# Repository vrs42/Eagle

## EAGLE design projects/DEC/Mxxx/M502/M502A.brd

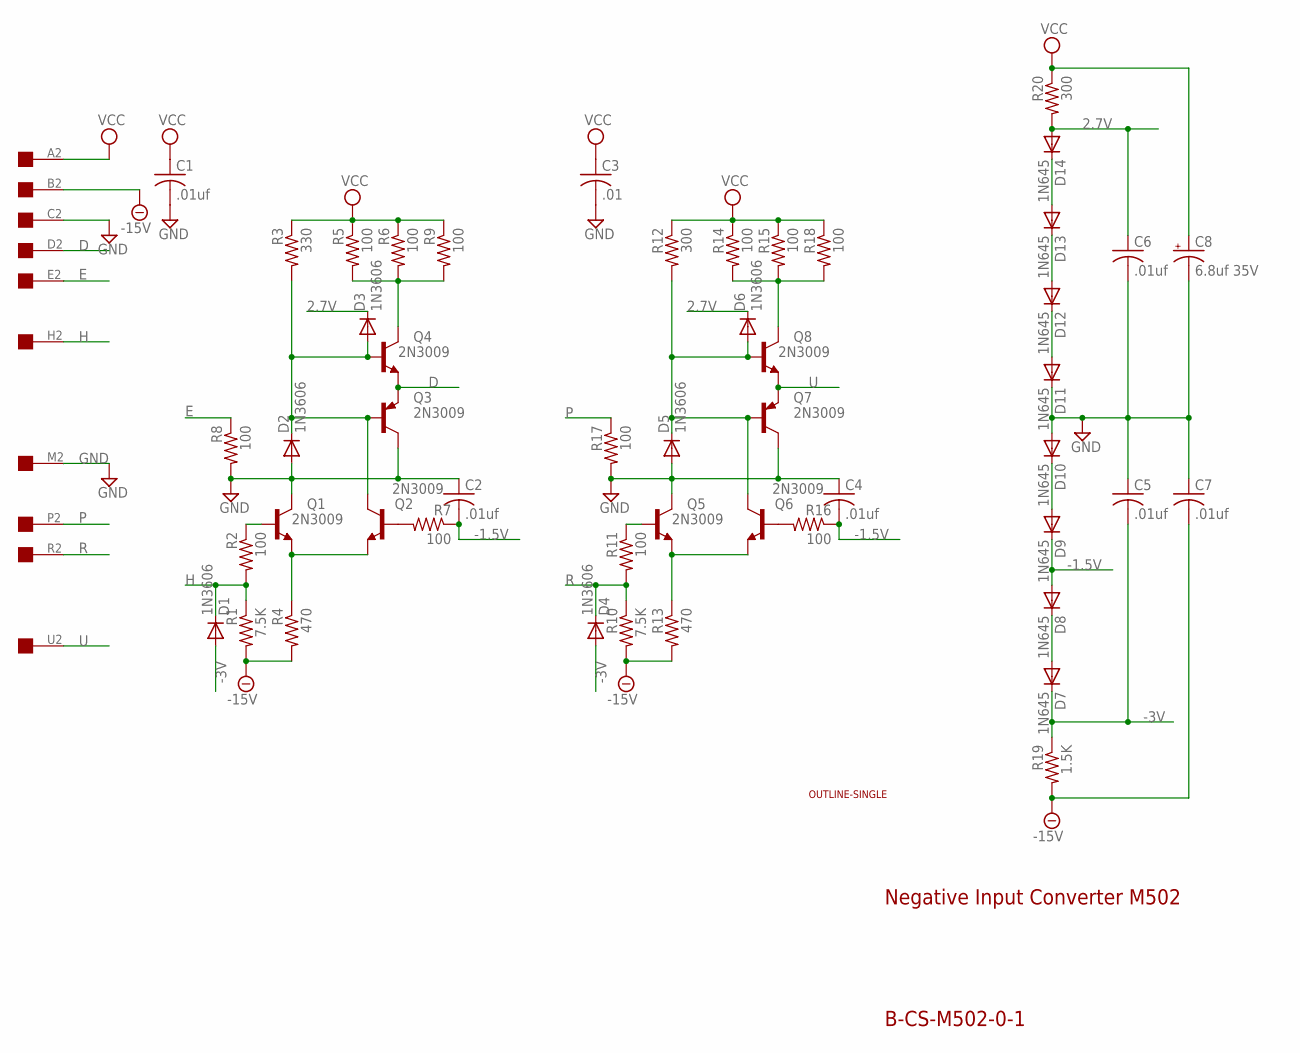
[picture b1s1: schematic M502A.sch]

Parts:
C1, C2, C4, C5, C6, C7: .01uf; C050-025X075
C3: .01; C050-025X075
C8: 6.8uf 35V; E15-5
D1, D2, D3, D4, D5, D6: 1N3606; DO41-10
D7, D8, D9, D10, D11, D12, D13, D14: 1N645; DO41-10
Q1, Q2, Q3, Q4, Q5, Q6, Q7, Q8: 2N3009; TO39
R1, R10: 7.5K; 0207/10
R2, R5, R6, R7, R8, R9, R11, R14, R15, R16, R17, R18: 100; 0207/10
R3: 330; 0207/10
R4, R13: 470; 0207/10
R12, R20: 300; 0207/10
R19: 1.5K; 0207/10
U$1: EDGE-1; EDGE-CON1
U$2: OUTLINE-SINGLE; SINGLE

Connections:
2.7V: C6.1, D3.C, D6.C, D14.A, R20.2
-1.5V: C2.2, C4.2, D8.A, D9.C, R7.1, R16.1
-3V: C5.2, D1.A, D4.A, D7.C, R19.1
-15V: C7.2, R1.2, R4.2, R10.2, R13.2, R19.2, U$1.B2
D: Q3.1 (E), Q4.1 (E), U$1.D2
E: R8.1, U$1.E2
GND: C1.2, C2.1, C3.2, C4.1, C5.1, C6.2, C7.1, C8.-, D2.A, D5.A, D10.A, D11.C, Q1.3 (C), Q3.3 (C), Q5.3 (C), Q7.3 (C), R8.2, R17.2, U$1.C2, U$1.M2
H: D1.C, R1.1, R2.2, U$1.H2
unnamed: Q4.3 (C), R5.2, R6.2, R9.2
unnamed: Q1.2 (B), R2.1
unnamed: Q5.1 (E), Q6.1 (E), R13.1
unnamed: Q1.1 (E), Q2.1 (E), R4.1
unnamed: D11.A, D12.C
unnamed: D2.C, D3.A, Q2.3 (C), Q3.2 (B), Q4.2 (B), R3.2
unnamed: D7.A, D8.C
unnamed: Q5.2 (B), R11.1
unnamed: D5.C, D6.A, Q6.3 (C), Q7.2 (B), Q8.2 (B), R12.2
unnamed: Q2.2 (B), R7.2
unnamed: D12.A, D13.C
unnamed: D9.A, D10.C
unnamed: Q8.3 (C), R14.2, R15.2, R18.2
unnamed: D13.A, D14.C
unnamed: Q6.2 (B), R16.2
P: R17.1, U$1.P2
R: D4.C, R10.1, R11.2, U$1.R2
U: Q7.1 (E), Q8.1 (E), U$1.U2
VCC: C1.1, C3.1, C8.+, R3.1, R5.1, R6.1, R9.1, R12.1, R14.1, R15.1, R18.1, R20.1, U$1.A2

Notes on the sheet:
Negative Input Converter M502
B-CS-M502-0-1

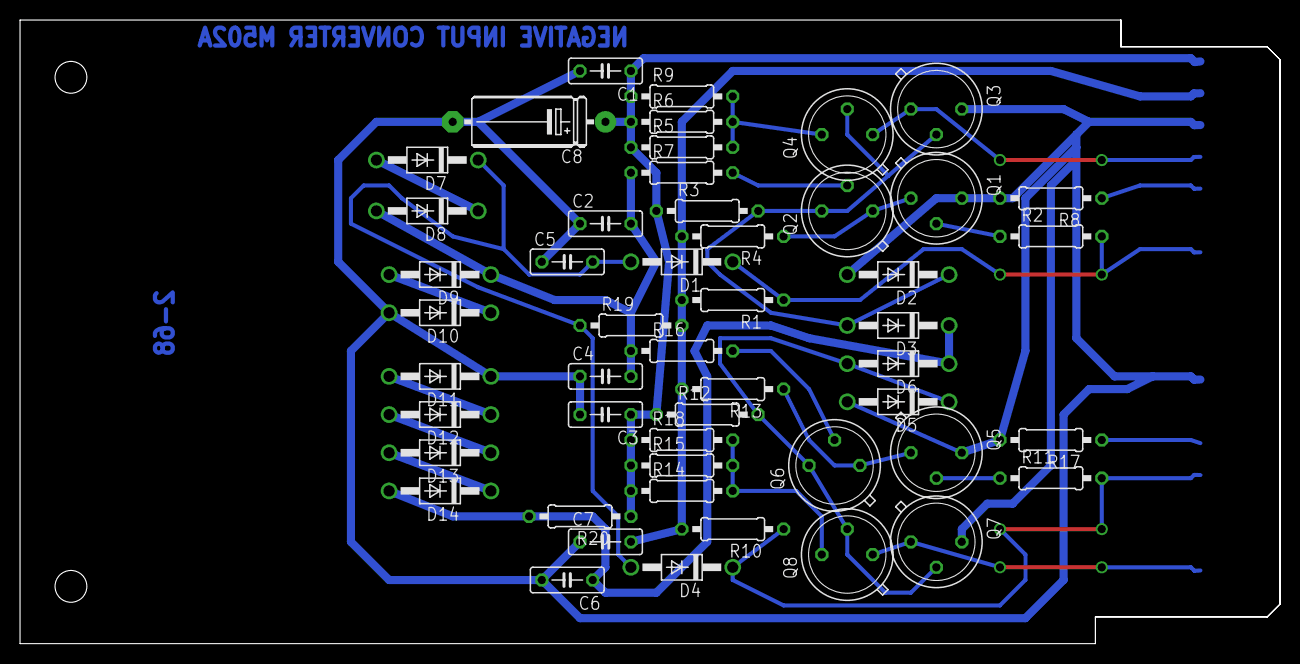
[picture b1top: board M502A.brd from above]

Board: 2 copper layers, 125.7 x 62.2 mm, 52 parts (0 on the bottom side), 27 nets.

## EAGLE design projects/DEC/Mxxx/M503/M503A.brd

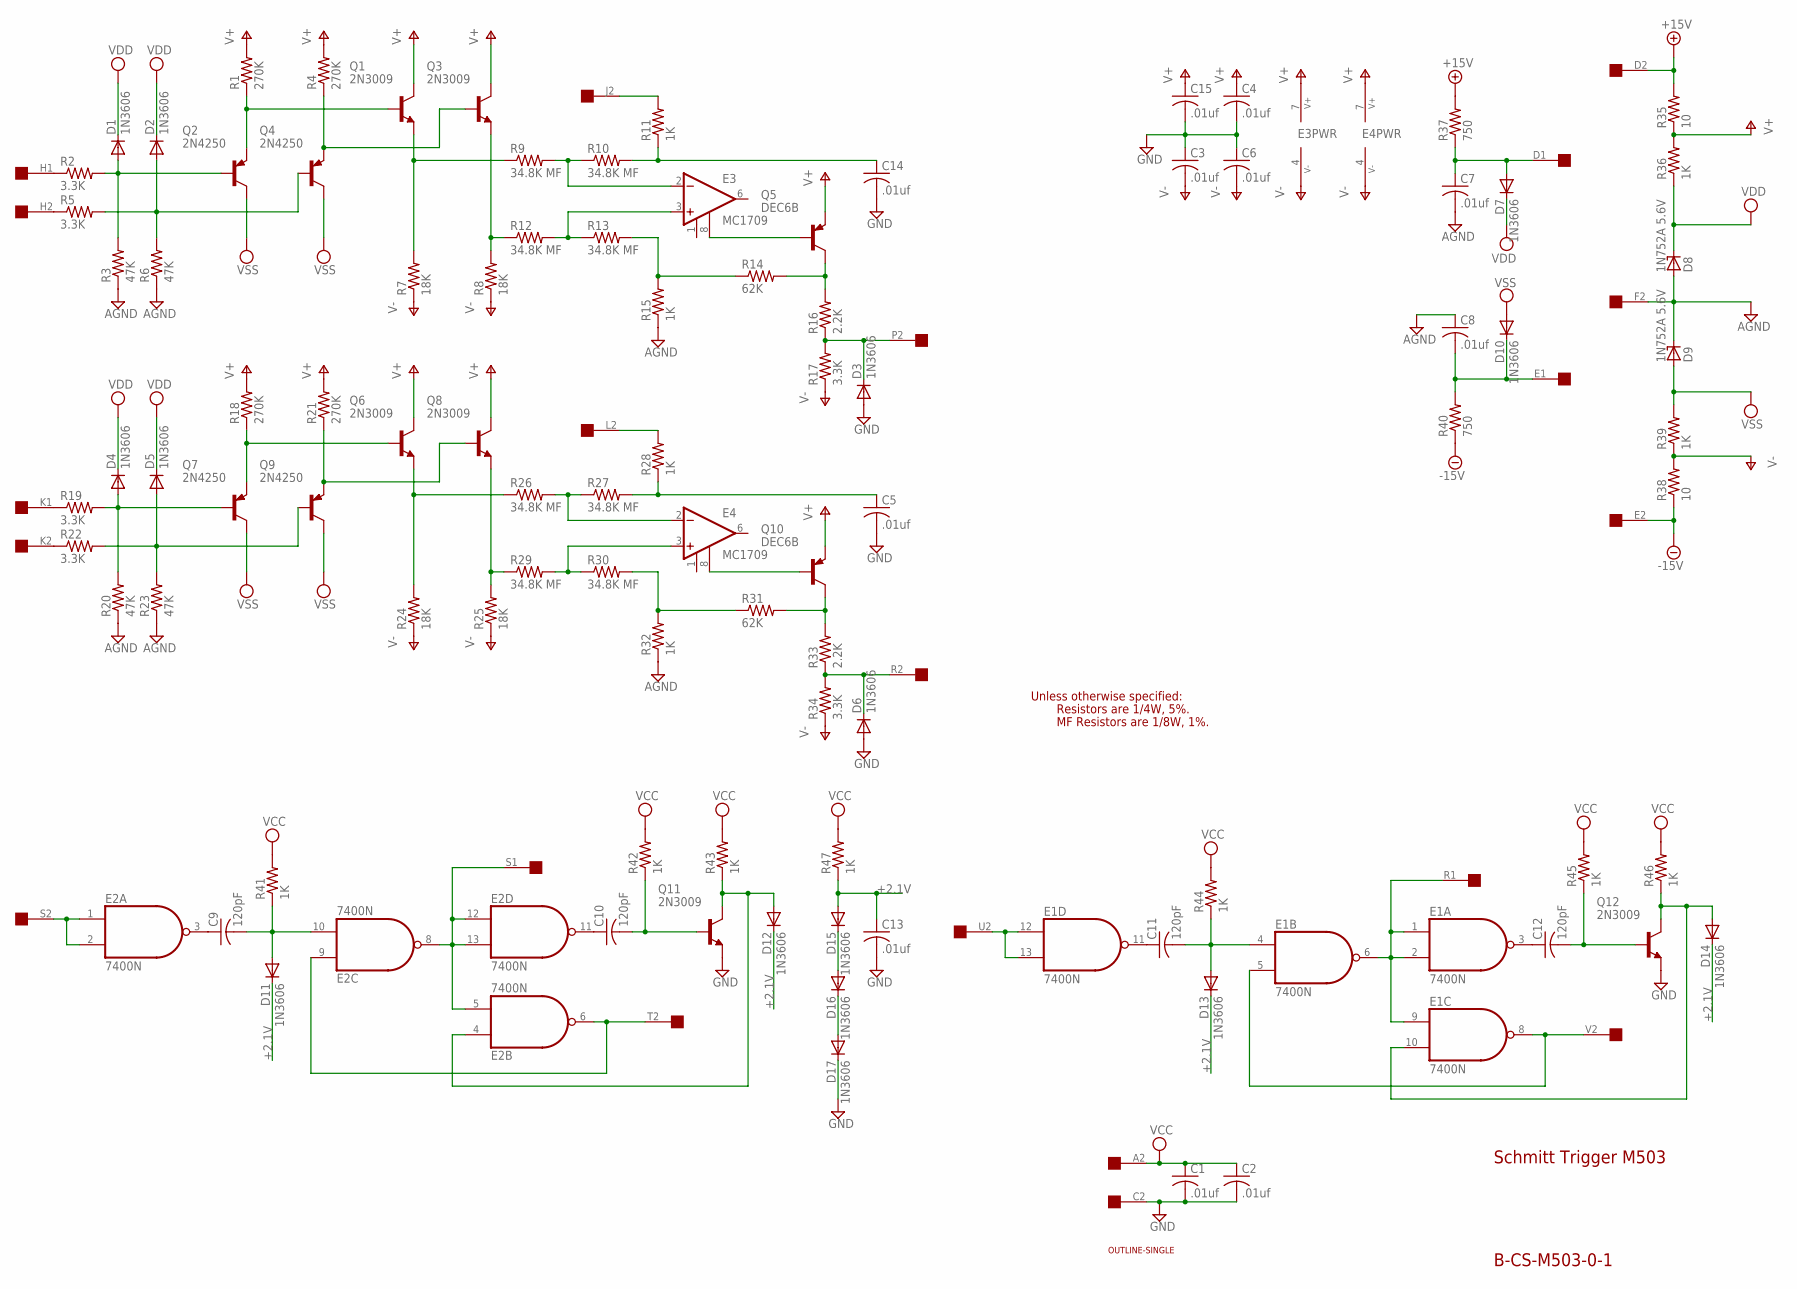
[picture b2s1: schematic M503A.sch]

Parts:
C1, C2: .01uf; C075-032X103
C3, C4, C5, C6, C7, C8, C13, C14, C15: .01uf; C050-025X075
C9, C10, C11, C12: 120pF; C050-025X075
D1, D2, D3, D4, D5, D6, D7, D10, D11, D12, D13, D14, D15, D16, D17: 1N3606; DO35-10
D8, D9: 1N752A 5.6V; DO35Z10
E1, E2: 7400N; DIL14
E3: MC1709; TO99C
E4: MC1709; TO99B
Q1, Q3, Q6, Q8, Q11, Q12: 2N3009; TO39
Q2, Q4, Q7, Q9: 2N4250; TO39
Q5, Q10: DEC6B; TO39
R1, R4, R18, R21: 270K; 0207/10
R2, R5, R17, R19, R22, R34: 3.3K; 0207/10
R3, R6, R20, R23: 47K; 0207/10
R7, R8, R24, R25: 18K; 0207/10
R9, R10, R12, R13, R26, R27, R29, R30: 34.8K MF; 0207/10
R11, R15, R28, R32, R36, R39, R41, R42, R43, R44, R45, R46, R47: 1K; 0207/10
R14, R31: 62K; 0207/10
R16, R33: 2.2K; 0207/10
R35, R38: 10; 0207/10
R37, R40: 750; 0207/10
U$2: SINGLE; EDGE-CON2
U$4: OUTLINE-SINGLE; SINGLE

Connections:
+2.1V: C13.1, D11.C, D12.C, D13.C, D14.C, D15.A, R47.1
+15V: R35.2, R37.2, U$2.D2
-15V: R38.1, R40.1, U$2.E2
AGND: C7.2, C8.1, D8.A, D9.C, R3.1, R6.1, R15.1, R20.1, R23.1, R32.1, U$2.F2
GND: C1.2, C2.2, C3.1, C4.2, C5.2, C6.1, C13.2, C14.2, C15.2, D3.A, D6.A, D17.C, E1.7 (GND), E2.7 (GND), Q11.1 (E), Q12.1 (E), U$2.C2
unnamed: E1.1 (I0), E1.2 (I1), E1.6 (O), E1.9 (I0), U$2.R1
unnamed: E1.5 (I1), E1.8 (O), U$2.V2
unnamed: E1.12 (I0), E1.13 (I1), U$2.U2
unnamed: C11.1, E1.11 (O)
unnamed: C11.2, D13.A, E1.4 (I0), R44.1
unnamed: D14.A, E1.10 (I1), Q12.3 (C), R46.1
unnamed: Q6.2 (B), Q7.1 (E), R18.1
unnamed: C12.2, Q12.2 (B), R45.1
unnamed: C12.1, E1.3 (O)
unnamed: E2.5 (I1), E2.8 (O), E2.12 (I0), E2.13 (I1), U$2.S1
unnamed: E2.6 (O), E2.9 (I0), U$2.T2
unnamed: C9.1, E2.3 (O)
unnamed: C9.2, D11.A, E2.10 (I1), R41.1
unnamed: E2.1 (I0), E2.2 (I1), U$2.S2
unnamed: Q1.2 (B), Q2.1 (E), R1.1
unnamed: C10.2, Q11.2 (B), R42.1
unnamed: C10.1, E2.11 (O)
unnamed: D12.A, E2.4 (I0), Q11.3 (C), R43.1
unnamed: D1.A, Q2.2 (B), R2.2, R3.2
unnamed: R2.1, U$2.H1
unnamed: Q1.1 (E), R7.2, R9.1
unnamed: R5.1, U$2.H2
unnamed: D2.A, Q4.2 (B), R5.2, R6.2
unnamed: Q3.2 (B), Q4.1 (E), R4.1
unnamed: Q3.1 (E), R8.2, R12.1
unnamed: E3.3 (+IN), R12.2, R13.1
unnamed: E3.2 (-IN), R9.2, R10.1
unnamed: C14.1, R10.2, R11.1
unnamed: R13.2, R14.1, R15.2
unnamed: E3.8 (CMP), Q5.2 (B)
unnamed: Q5.3 (C), R14.2, R16.2
unnamed: R11.2, U$2.J2
unnamed: D3.C, R16.1, R17.2, U$2.P2
unnamed: D4.A, Q7.2 (B), R19.2, R20.2
unnamed: R22.1, U$2.K2
unnamed: Q6.1 (E), R24.2, R26.1
unnamed: R19.1, U$2.K1
unnamed: D5.A, Q9.2 (B), R22.2, R23.2
unnamed: Q8.2 (B), Q9.1 (E), R21.1
unnamed: Q8.1 (E), R25.2, R29.1
unnamed: E4.3 (+IN), R29.2, R30.1
unnamed: E4.2 (-IN), R26.2, R27.1
unnamed: C5.1, R27.2, R28.1
unnamed: R30.2, R31.1, R32.2
unnamed: E4.8 (CMP), Q10.2 (B)
unnamed: Q10.3 (C), R31.2, R33.2
unnamed: R28.2, U$2.L2
unnamed: D6.C, R33.1, R34.2, U$2.R2
unnamed: C7.1, D7.A, R37.1, U$2.D1
unnamed: C8.2, D10.C, R40.2, U$2.E1
unnamed: D15.C, D16.A
unnamed: D16.C, D17.A
V+: C4.1, C15.1, E3.7 (+10V), E4.7 (+10V), Q1.3 (C), Q3.3 (C), Q5.1 (E), Q6.3 (C), Q8.3 (C), Q10.1 (E), R1.2, R4.2, R18.2, R21.2, R35.1, R36.2
V-: C3.2, C6.2, E3.4 (-15V), E4.4 (-15V), R7.1, R8.1, R17.1, R24.1, R25.1, R34.1, R38.2, R39.1
VCC: C1.1, C2.1, E1.14 (VCC), E2.14 (VCC), R41.2, R42.2, R43.2, R44.2, R45.2, R46.2, R47.2, U$2.A2
VDD: D1.C, D2.C, D4.C, D5.C, D7.C, D8.C, R36.1
VSS: D9.A, D10.A, Q2.3 (C), Q4.3 (C), Q7.3 (C), Q9.3 (C), R39.2

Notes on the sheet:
Schmitt Trigger M503
B-CS-M503-0-1
Unless otherwise specified:
Resistors are 1/4W, 5%.
MF Resistors are 1/8W, 1%.

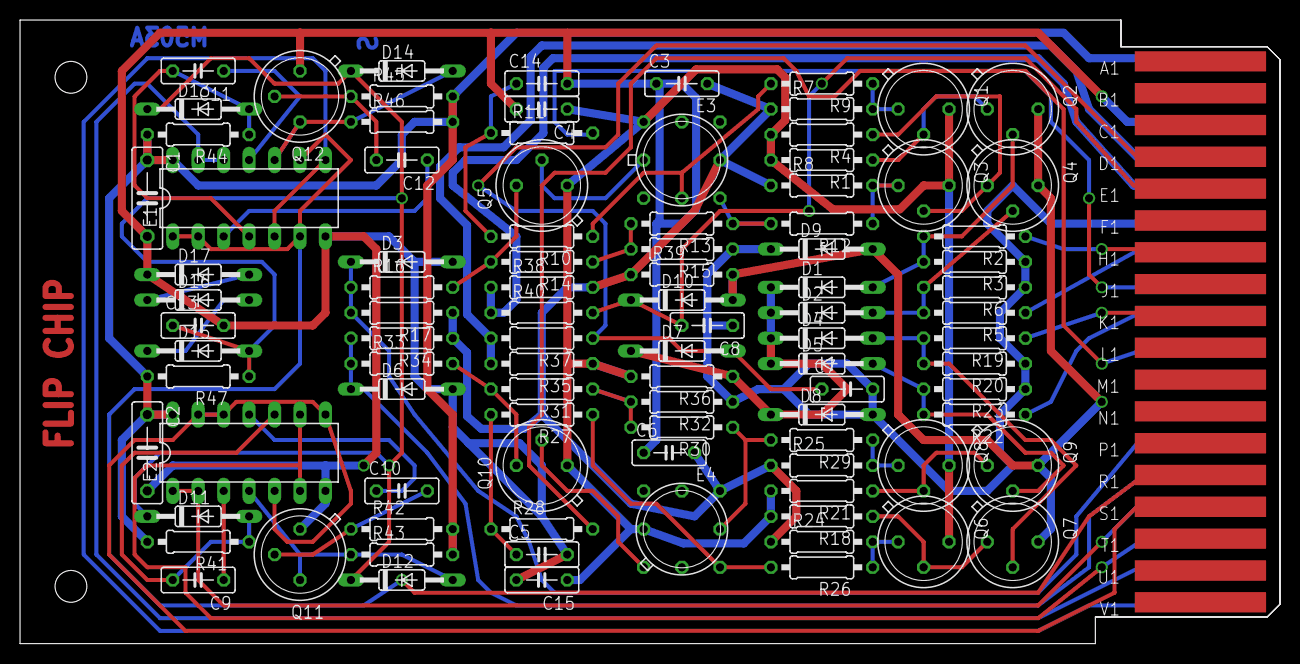
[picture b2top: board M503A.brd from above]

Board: 2 copper layers, 125.7 x 62.2 mm, 98 parts (0 on the bottom side), 62 nets.

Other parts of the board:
U$1: FLIPCHIP

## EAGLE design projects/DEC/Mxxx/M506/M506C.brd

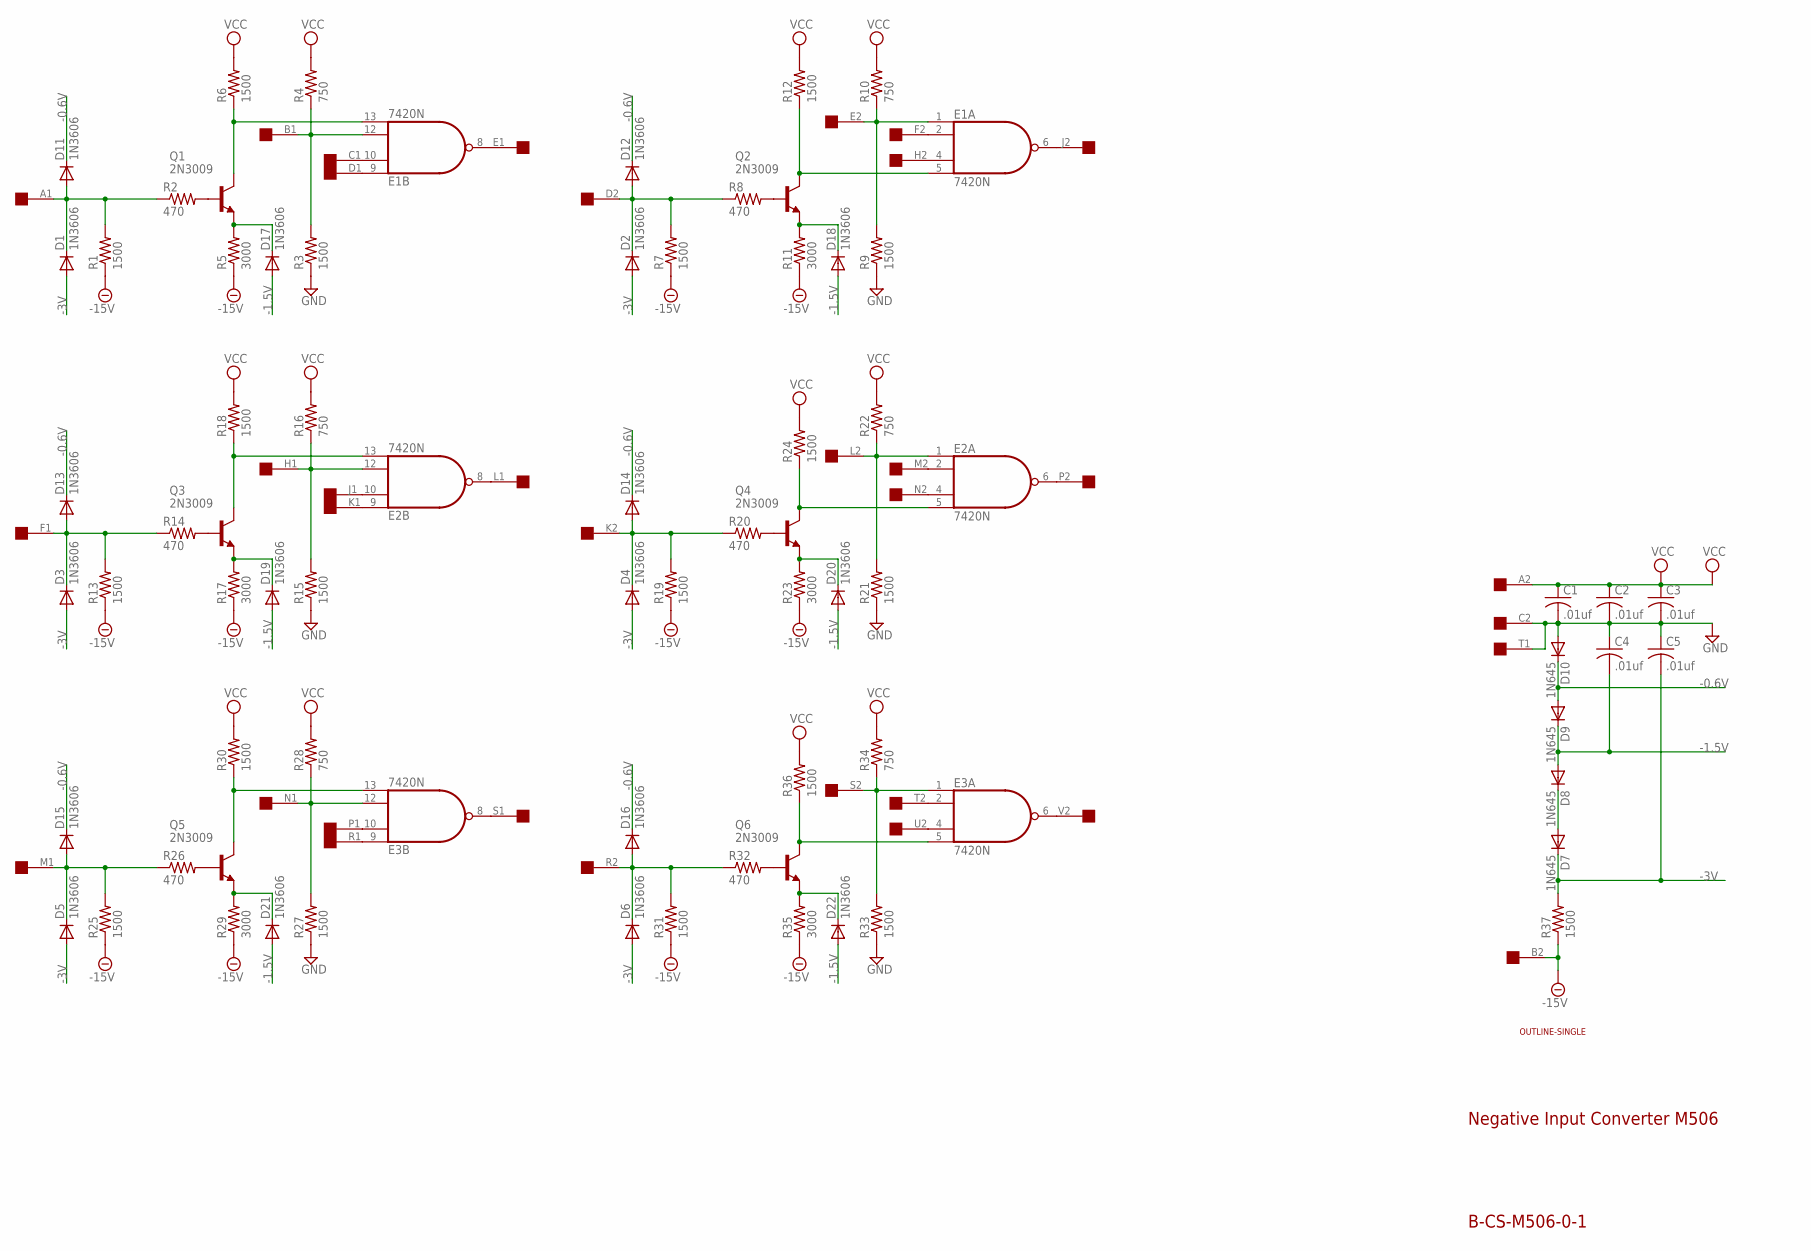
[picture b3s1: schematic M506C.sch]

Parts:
C1, C2, C3, C4, C5: .01uf; C050-025X075
D1, D2, D3, D4, D5, D6, D11, D12, D13, D14, D15, D16, D17, D18, D19, D20, D21, D22: 1N3606; DO35-10
D7, D8, D9, D10: 1N645; DO35-10
E1, E2, E3: 7420N; DIL14
Q1, Q2, Q3, Q4, Q5, Q6: 2N3009; TO39
R1, R3, R6, R7, R9, R12, R13, R15, R18, R19, R21, R24, R25, R27, R30, R31, R33, R36, R37: 1500; 0207/10
R2, R8, R14, R20, R26, R32: 470; 0207/10
R4, R10, R16, R22, R28, R34: 750; 0207/10
R5, R11, R17, R23, R29, R35: 3000; 0207/10
U$2: SINGLE; EDGE-CON2
U$4: OUTLINE-SINGLE; SINGLE

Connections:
-0.6V: D9.A, D10.C, D11.C, D12.C, D13.C, D14.C, D15.C, D16.C
-1.5V: C4.2, D8.A, D9.C, D17.A, D18.A, D19.A, D20.A, D21.A, D22.A
-3V: C5.2, D1.A, D2.A, D3.A, D4.A, D5.A, D6.A, D7.C, R37.2
-15V: R1.1, R5.1, R7.1, R11.1, R13.1, R17.1, R19.1, R23.1, R25.1, R29.1, R31.1, R35.1, R37.1, U$2.B2
GND: C1.2, C2.2, C3.2, C4.1, C5.1, D10.A, E1.7 (GND), E2.7 (GND), E3.7 (GND), R3.1, R9.1, R15.1, R21.1, R27.1, R33.1, U$2.C2, U$2.T1
unnamed: D1.C, D11.A, R1.2, R2.1, U$2.A1
unnamed: Q1.2 (B), R2.2
unnamed: D17.C, Q1.1 (E), R5.2
unnamed: E1.12 (I2), R3.2, R4.1, U$2.B1
unnamed: E1.13 (I3), Q1.3 (C), R6.1
unnamed: E1.10 (I1), U$2.C1
unnamed: E1.9 (I0), U$2.D1
unnamed: E1.8 (O), U$2.E1
unnamed: D2.C, D12.A, R7.2, R8.1, U$2.D2
unnamed: Q2.2 (B), R8.2
unnamed: D18.C, Q2.1 (E), R11.2
unnamed: E1.1 (I0), R9.2, R10.1, U$2.E2
unnamed: E1.5 (I3), Q2.3 (C), R12.1
unnamed: E1.6 (O), U$2.J2
unnamed: E1.2 (I1), U$2.F2
unnamed: E1.4 (I2), U$2.H2
unnamed: D3.C, D13.A, R13.2, R14.1, U$2.F1
unnamed: Q3.2 (B), R14.2
unnamed: D19.C, Q3.1 (E), R17.2
unnamed: E2.12 (I2), R15.2, R16.1, U$2.H1
unnamed: E2.13 (I3), Q3.3 (C), R18.1
unnamed: D5.C, D15.A, R25.2, R26.1, U$2.M1
unnamed: Q5.2 (B), R26.2
unnamed: D21.C, Q5.1 (E), R29.2
unnamed: D4.C, D14.A, R19.2, R20.1, U$2.K2
unnamed: Q4.2 (B), R20.2
unnamed: D20.C, Q4.1 (E), R23.2
unnamed: E2.1 (I0), R21.2, R22.1, U$2.L2
unnamed: E2.5 (I3), Q4.3 (C), R24.1
unnamed: E3.12 (I2), R27.2, R28.1, U$2.N1
unnamed: E3.13 (I3), Q5.3 (C), R30.1
unnamed: D6.C, D16.A, R31.2, R32.1, U$2.R2
unnamed: Q6.2 (B), R32.2
unnamed: D22.C, Q6.1 (E), R35.2
unnamed: E3.1 (I0), R33.2, R34.1, U$2.S2
unnamed: E3.5 (I3), Q6.3 (C), R36.1
unnamed: E2.10 (I1), U$2.J1
unnamed: E2.9 (I0), U$2.K1
unnamed: E3.10 (I1), U$2.P1
unnamed: E3.9 (I0), U$2.R1
unnamed: E2.8 (O), U$2.L1
unnamed: E3.8 (O), U$2.S1
unnamed: E2.2 (I1), U$2.M2
unnamed: E2.4 (I2), U$2.N2
unnamed: E2.6 (O), U$2.P2
unnamed: E3.4 (I2), U$2.U2
unnamed: E3.6 (O), U$2.V2
unnamed: E3.2 (I1), U$2.T2
unnamed: D7.A, D8.C
VCC: C1.1, C2.1, C3.1, E1.14 (VCC), E2.14 (VCC), E3.14 (VCC), R4.2, R6.2, R10.2, R12.2, R16.2, R18.2, R22.2, R24.2, R28.2, R30.2, R34.2, R36.2, U$2.A2

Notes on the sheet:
Negative Input Converter M506
B-CS-M506-0-1

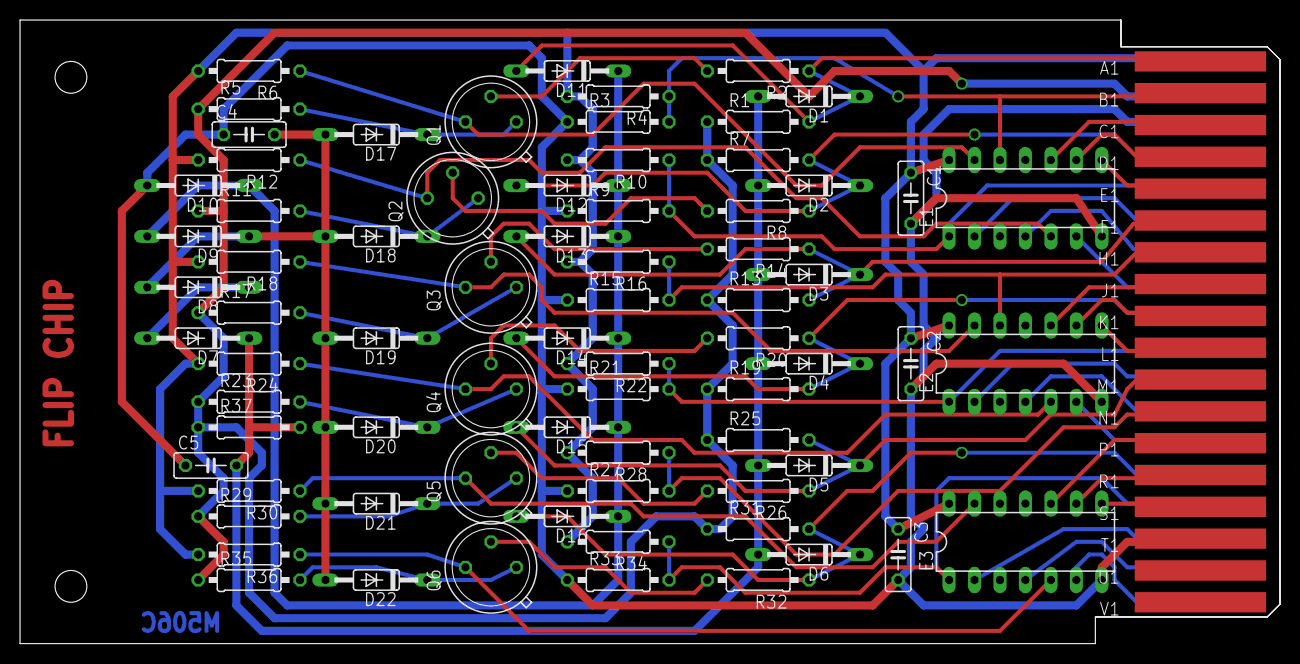
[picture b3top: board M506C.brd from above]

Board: 2 copper layers, 125.7 x 62.2 mm, 76 parts (0 on the bottom side), 55 nets.

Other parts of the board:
U$1: FLIPCHIP
